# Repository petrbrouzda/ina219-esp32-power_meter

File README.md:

# Měřič spotřeby elektřiny s ESP32 a INA-219 (ina219-esp32-power_meter)

Aplikace pro měřič spotřeby s ESP32 (LilyGO TTGO T-Display) a obvodem INA-219.

Více informací zde: https://pebrou.wordpress.com/2020/08/29/stavime-chytry-meric-spotreby-s-esp32-a-modulem-ina219/

- Vlastní základní (nepřipojená na internet) aplikace je v ina219_app_g1/
- V ina219_app_wifi_g2 je verze, která odesílá data na internet. 
- V iic_scanner/ je jednoduchý scanner I2C sběrnice pro vyhledání adresy modulu INA219 , pokud není na standardní adrese.
- V schema_a_deska/ najdete schema zapojení. Návrh desky tam teď není.

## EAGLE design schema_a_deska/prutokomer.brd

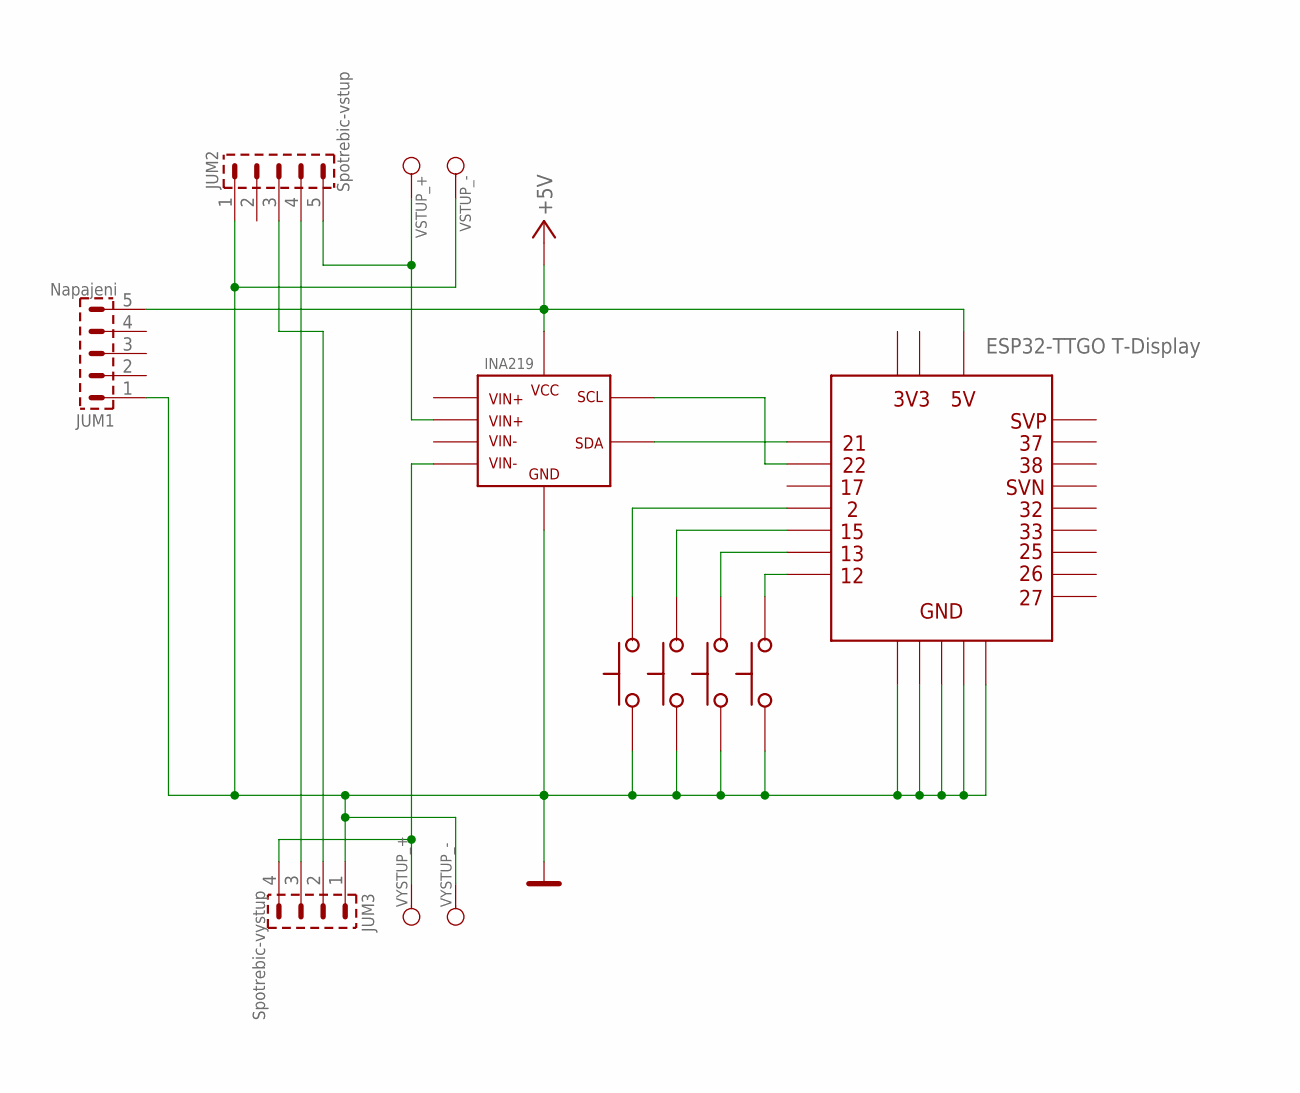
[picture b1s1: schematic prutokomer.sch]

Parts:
JUM1: Napajeni; S1G5_JUM
JUM2: Spotrebic-vstup; S1G5_JUM
JUM3: Spotrebic-vystup; S1G4_JUM
SW1, SW2, SW3, SW4: TLACITKO
U$1: INA219
U$2: ESP32_TTGOT-DISPLAY; ESP32-TTGO-TDISPLAY
VSTUP_+: PAD_1
VSTUP_-: PAD_1
VYSTUP_+: PAD_1
VYSTUP_-: PAD_1

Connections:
+5V: JUM1.5, U$1.VCC, U$2.5V
GND: JUM1.1, JUM2.1, JUM3.1, SW1.1, SW2.1, SW3.1, SW4.1, U$1.GND, U$2.GND1, U$2.GND2, U$2.GND3, U$2.GND4, U$2.GND5, VSTUP_-.1, VYSTUP_-.1
unnamed: JUM2.5, U$1...VIN+ (.VIN+), VSTUP_+.1
unnamed: JUM3.4, U$1...VIN- (.VIN-), VYSTUP_+.1
unnamed: U$1.SDA, U$2.21
unnamed: U$1.SCL, U$2.22
unnamed: JUM2.4, JUM3.3
unnamed: JUM2.3, JUM3.2
unnamed: SW4.2, U$2.12
unnamed: SW3.2, U$2.13
unnamed: SW2.2, U$2.15
unnamed: SW1.2, U$2.2

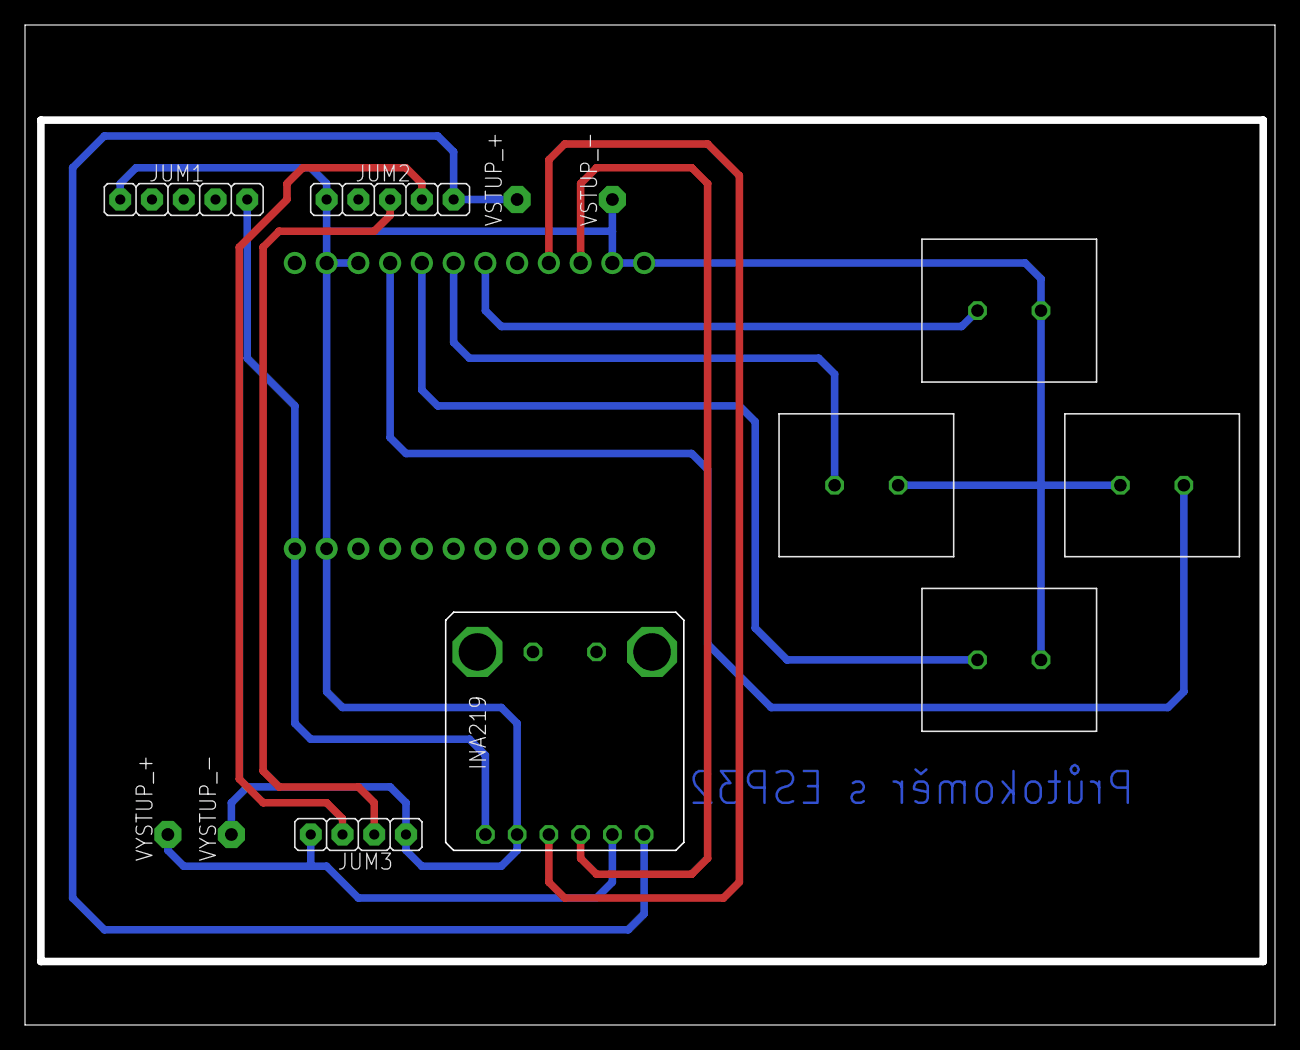
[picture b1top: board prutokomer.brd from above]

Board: 2 copper layers, 100.0 x 80.0 mm, 13 parts (0 on the bottom side), 12 nets.

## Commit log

2020-08-28 prvni verejne zdrojaky
2020-08-28 nadbytecne, vzdy se nastavi
2020-08-28 - osetreni chuyby pri nenalezeni INA219 - zacisteni zdrojaku, doplneni komentaru
2020-08-28 komentare
2020-08-28 zarovnani
2020-08-28 rozliseni -> rozsah
2020-08-28 spotrebic/zdroj -> load/source
2020-08-28 schema a deska
2020-08-28 odkazy na moduly
2020-08-28 nadbytecne
2020-08-29 - doplneni .h pro .ino, neb se to ve VsCode negenerovalo - moznost nastavit low/high threshold v menu - prejmenovani souboru
2020-08-29 prejmenovani
2020-08-29 prejmenovani pro case sensitivitu
2020-08-29 - prechod na ukladani sumarnich hodnot v long long - nova stranka s informaci o casu a spotrebe v low power / high power - merici obrazovky se prekresluji bez mazani
2020-08-29 odstraneni logovani pri konverzich cisel
2020-08-29 Dalsi obrazovka s poctem high-power udalosti a delkou posledni z nich.
2020-08-29 nová obrazovka s informacemi o úsecích vysoké spotřeby
2020-09-01 popis
2020-09-01 čeština
2020-09-01 překlep
2020-09-01 - rozbití obrazovky s max/min napětím a proudem na dvě; je tedy 5 obrazovek - měření relativního času nejnižšího a nejvyššího napětí - měření relativního času nejvyššího proudu
2020-09-01 překlep v nadpisu
2020-09-10 verze se zapisem dat na server
2020-09-11 Plná funkčnost dle plánu
2020-09-14 lf na konec radku
2020-09-14 novejsi verze RA core
2020-09-14 lepsi konvence pojmenovani souboru
2020-09-15 vypnuti debug logu
2020-09-15 přesun logování do callbacku
2020-09-15 mDns
2020-09-15 - odstraneni mDNS - opakovane odeslani v pripade chyby
2020-09-16 odstraneni debug vypisu
2020-09-17 přechod na I2C na portech 25, 26
2020-09-17 README
2020-09-17 ještě jednou README
2020-10-10 aktualizace core 3.2.1
2020-10-10 core 3.2.2
2021-02-15 výměna knihoven Ratatoskr za aktuální verzi 5.1.2
2021-02-15 nastaveni gitignore

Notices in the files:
parts and their libraries:
Copyright (C) PaJa 2011-2014
Copyright (C) PaJa 2001-2014
